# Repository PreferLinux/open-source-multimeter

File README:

The schematics and PCB layout are done in KiCAD.

Please see https://hackaday.io/project/10820-open-source-multimeter for details. There are also details in the schematics.

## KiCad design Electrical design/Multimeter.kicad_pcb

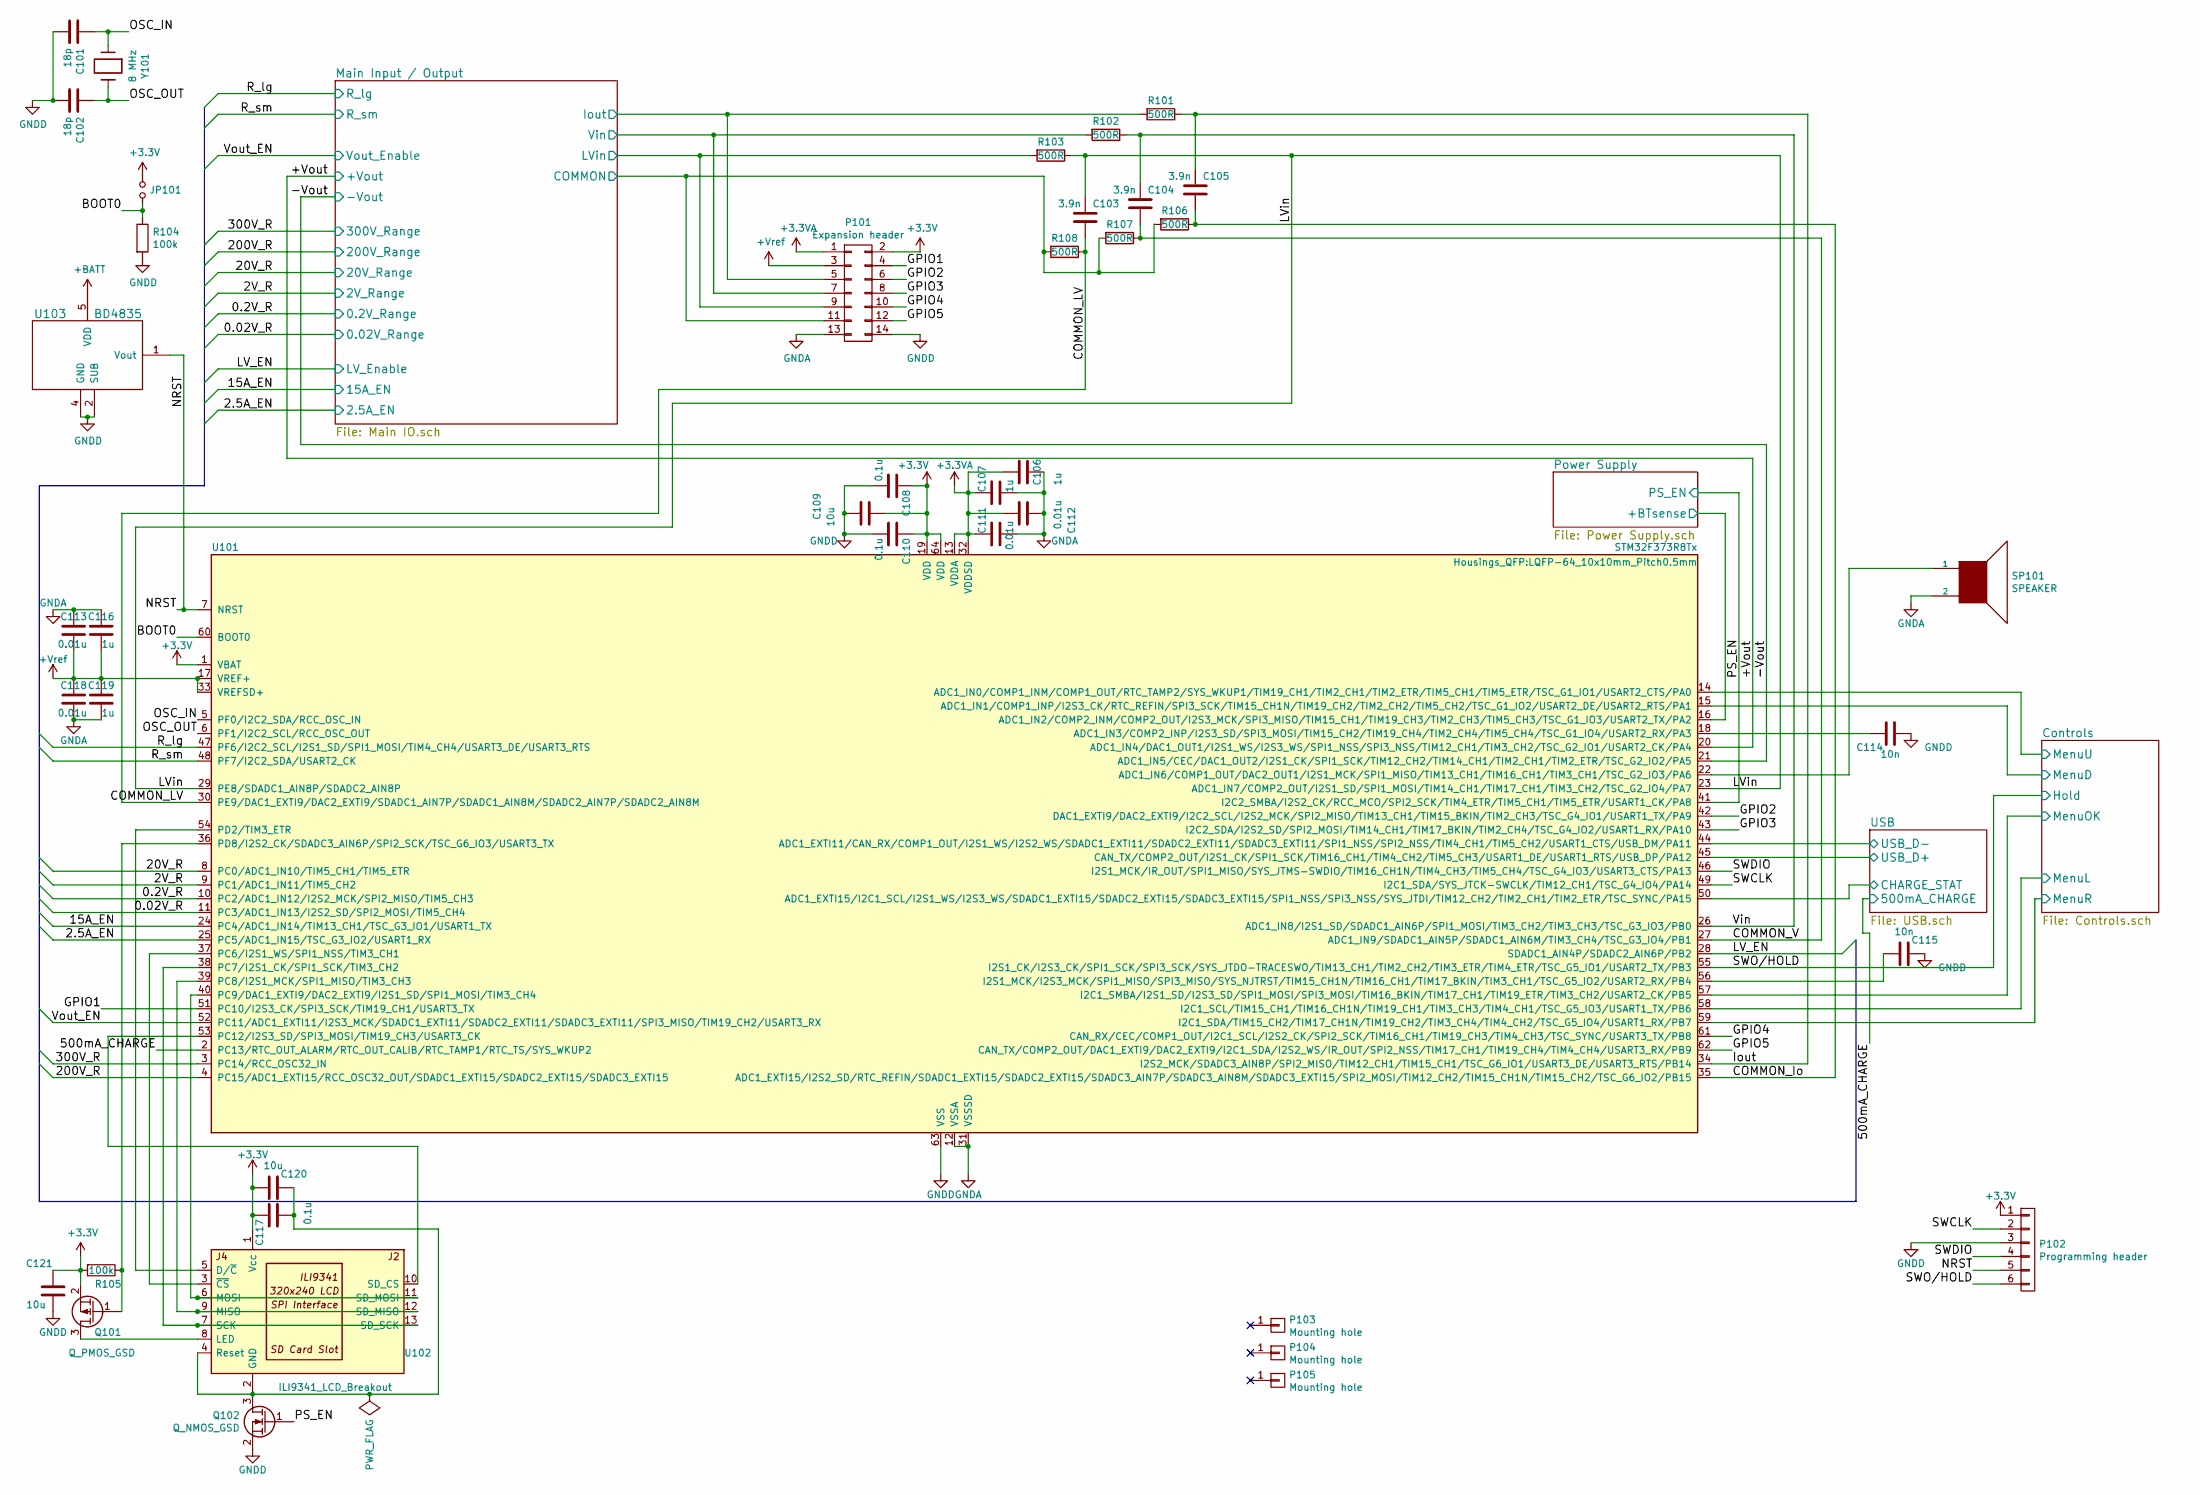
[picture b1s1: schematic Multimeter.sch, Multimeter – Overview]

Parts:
C101, C102: 18p; SMDuniversal_0603to0805_HandSoldering
C103, C104, C105: 3.9n; SMDuniversal_0603to0805_HandSoldering
C106, C107, C116, C119: 1u; SMDuniversal_0603to0805_HandSoldering
C108, C110, C117: 0.1u; SMDuniversal_0603to0805_HandSoldering
C109, C120, C121: 10u; SMDuniversal_0603to1206_HandSoldering
C111, C112, C113, C118: 0.01u; SMDuniversal_0603to0805_HandSoldering
C114, C115: 10n; SMDuniversal_0603to0805_HandSoldering
JP101: BOOT0; Pin_Header_Straight_1x02
P101: Expansion header; Pin_Header_Straight_2x07
P102: Programming header; Pin_Header_Straight_1x06
P103, P104, P105: Mounting hole; MountingHole_3.2mm_M3
Q101: Q_PMOS_GSD; SOT-23
Q102: Q_NMOS_GSD; SOT-23
R101, R102, R103, R106, R107, R108: 500R; SMDuniversal_0603to1210_HandSoldering
R104, R105: 100k; SMDuniversal_0603to1210_HandSoldering
SP101: SPEAKER; Pin_Header_Straight_1x02
U101: STM32F373R8Tx; LQFP-64_10x10mm_Pitch0.5mm
U102: ILI9341_LCD_Breakout
U103: BD4835; VSOF5_HandSoldering
Y101: 8 MHz; Crystal_HC49-SD_SMD

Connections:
+3.3VA: C106.2, C107.2, C111.2, C112.2, P101.1, U101.13 (VDDA), U101.32 (VDDSD); also elsewhere on the board
+3V3: C108.1, C109.2, C110.1, C117.1, C120.2, C121.1, JP101.1, P101.2, P102.1, Q101.2 (S), R105.2, U101.1 (VBAT), U101.19 (VDD), U101.64 (VDD), U102.1 (Vcc); also elsewhere on the board
+BATT: U103.5 (VDD); also elsewhere on the board
+Vref: C113.1, C116.1, C118.2, C119.2, P101.3, U101.17 (VREF+), U101.33 (VREFSD+); also elsewhere on the board
/0.2V_R: U101.10 (PC2/ADC1_IN12/I2S2_MCK/SPI2_MISO/TIM5_C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); also elsewhere on the board
/0.02V_R: U101.11 (PC3/ADC1_IN13/I2S2_SD/SPI2_MOSI/TIM5_CH4); also elsewhere on the board
/2.5A_EN: U101.25 (PC5/ADC1_IN15/TSC_G3_IO2/USART1_RX); also elsewhere on the board
/2V_R: U101.9 (PC1/ADC1_IN11/TIM5_CH2); also elsewhere on the board
/15A_EN: U101.24 (PC4/ADC1_IN14/TIM13_CH1/TSC_G3_IO1/USAR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); also elsewhere on the board
/20V_R: U101.8 (PC0/ADC1_IN10/TIM5_CH1/TIM5_ETR); also elsewhere on the board
/200V_R: U101.4 (PC15/ADC1_EXTI15/RCC_OSC32_OUT/SDADC1_E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); also elsewhere on the board
/300V_R: U101.3 (PC14/RCC_OSC32_IN); also elsewhere on the board
/500mA_CHARGE: U101.2 (PC13/RTC_OUT_ALARM/RTC_OUT_CALIB/RTC_TA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); also elsewhere on the board
/+Vout: U101.20 (ADC1_IN4/DAC1_OUT1/I2S1_WS/I2S3_WS/SPI1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); also elsewhere on the board
/-Vout: U101.21 (ADC1_IN5/CEC/DAC1_OUT2/I2S1_CK/SPI1_SCK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); also elsewhere on the board
/BOOT0: JP101.2, R104.1, U101.60 (BOOT0)
/COMMON_Io: C105.2, R106.1, U101.35 (ADC1_EXTI15/I2S2_SD/RTC_REFIN/SDADC1_EX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)
/COMMON_LV: C103.2, R108.1, U101.30 (PE9/DAC1_EXTI9/DAC2_EXTI9/SDADC1_AIN7P/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)
/COMMON_V: C104.2, R107.1, U101.27 (ADC1_IN9/SDADC1_AIN5P/SDADC1_AIN6M/TIM3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)
/Controls/MenuD: U101.15 (ADC1_IN1/COMP1_INP/I2S3_CK/RTC_REFIN/SP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); also elsewhere on the board
/Controls/MenuL: U101.58 (I2C1_SCL/TIM15_CH1/TIM16_CH1N/TIM19_CH1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); also elsewhere on the board
/Controls/MenuOK: U101.57 (I2C1_SMBA/I2S1_SD/I2S3_SD/SPI1_MOSI/SPI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); also elsewhere on the board
/Controls/MenuR: U101.59 (I2C1_SDA/TIM15_CH2/TIM17_CH1N/TIM19_CH2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); also elsewhere on the board
/Controls/MenuU: U101.14 (ADC1_IN0/COMP1_INM/COMP1_OUT/RTC_TAMP2/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); also elsewhere on the board
/GPIO1: P101.4, U101.51 (PC10/I2S3_CK/SPI3_SCK/TIM19_CH1/USART3_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)
/GPIO2: P101.6, U101.42 (DAC1_EXTI9/DAC2_EXTI9/I2C2_SCL/I2S2_MCK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)
/GPIO3: P101.8, U101.43 (I2C2_SDA/I2S2_SD/SPI2_MOSI/TIM14_CH1/TI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)
/GPIO4: P101.10, U101.61 (CAN_RX/CEC/COMP1_OUT/I2C1_SCL/I2S2_CK/S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)
/GPIO5: P101.12, U101.62 (CAN_TX/COMP2_OUT/DAC1_EXTI9/DAC2_EXTI9/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)
/Iout: C105.1, R101.1, U101.34 (I2S2_MCK/SDADC3_AIN8P/SPI2_MISO/TIM12_C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)
/LV_EN: U101.28 (SDADC1_AIN4P/SDADC2_AIN6P/PB2); also elsewhere on the board
/LVin: C103.1, R103.1, U101.23 (ADC1_IN7/COMP2_OUT/I2S1_SD/SPI1_MOSI/TI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), U101.29 (PE8/SDADC1_AIN8P/SDADC2_AIN8P)
/Main Input / Output/COMMON: P101.11, R106.2, R107.2, R108.2; also elsewhere on the board
/Main Input / Output/Iout: P101.5, R101.2; also elsewhere on the board
/Main Input / Output/LVin: P101.9, R103.2; also elsewhere on the board
/Main Input / Output/Vin: P101.7, R102.2; also elsewhere on the board
/NRST: P102.5, U101.7 (NRST), U103.1 (Vout)
/OSC_IN: C101.1, U101.5 (PF0/I2C2_SDA/RCC_OSC_IN), Y101.1
/OSC_OUT: C102.1, U101.6 (PF1/I2C2_SCL/RCC_OSC_OUT), Y101.2
/PS_EN: Q102.1 (G), U101.41 (I2C2_SMBA/I2S2_CK/RCC_MCO/SPI2_SCK/TIM4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); also elsewhere on the board
/Power Supply/+BTsense: U101.16 (ADC1_IN2/COMP2_INM/COMP2_OUT/I2S3_MCK/S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); also elsewhere on the board
/R_lg: U101.47 (PF6/I2C2_SCL/I2S1_SD/SPI1_MOSI/TIM4_CH4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); also elsewhere on the board
/R_sm: U101.48 (PF7/I2C2_SDA/USART2_CK); also elsewhere on the board
/SWCLK: P102.2, U101.49 (I2C1_SDA/SYS_JTCK-SWCLK/TIM12_CH1/TSC_G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)
/SWDIO: P102.4, U101.46 (I2S1_MCK/IR_OUT/SPI1_MISO/SYS_JTMS-SWDI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)
/SWO/HOLD: P102.6, U101.55 (I2S1_CK/I2S3_CK/SPI1_SCK/SPI3_SCK/SYS_J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); also elsewhere on the board
/USB/CHARGE_STAT: U101.50 (ADC1_EXTI15/I2C1_SCL/I2S1_WS/I2S3_WS/SD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); also elsewhere on the board
/USB/USB_D+: U101.45 (CAN_TX/COMP2_OUT/I2S1_CK/SPI1_SCK/TIM16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); also elsewhere on the board
/USB/USB_D-: U101.44 (ADC1_EXTI11/CAN_RX/COMP1_OUT/I2S1_WS/I2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); also elsewhere on the board
/Vin: C104.1, R102.1, U101.26 (ADC1_IN8/I2S1_SD/SDADC1_AIN6P/SPI1_MOSI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)
/Vout_EN: U101.52 (PC11/ADC1_EXTI11/I2S3_MCK/SDADC1_EXTI11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); also elsewhere on the board
GNDA: C106.1, C107.1, C111.1, C112.1, C113.2, C116.2, C118.1, C119.1, P101.13, SP101.2, U101.12 (VSSA), U101.31 (VSSSD); also elsewhere on the board
GNDD: C101.2, C102.2, C108.2, C109.1, C110.2, C114.1, C115.1, C121.2, P101.14, P102.3, Q102.2 (S), R104.2, U101.63 (VSS), U103.2 (SUB), U103.4 (GND); also elsewhere on the board
unnamed: C114.2, U101.18 (ADC1_IN3/COMP2_INP/I2S3_SD/SPI3_MOSI/TI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)
unnamed: C115.2, U101.56 (I2S1_MCK/I2S3_MCK/SPI1_MISO/SPI3_MISO/S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)
unnamed: C117.2, C120.1, Q102.3 (D), U102.2 (GND), U102.4 (Reset)
unnamed: Q101.1 (G), R105.1, U101.36 (PD8/I2S2_CK/SDADC3_AIN6P/SPI2_SCK/TSC_G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)
unnamed: Q101.3 (D), U102.8 (LED)
unnamed: SP101.1, U101.22 (ADC1_IN6/COMP1_OUT/DAC2_OUT1/I2S1_MCK/S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)
unnamed: U101.37 (PC6/I2S1_WS/SPI1_NSS/TIM3_CH1), U102.3 (~CS)
unnamed: U101.38 (PC7/I2S1_CK/SPI1_SCK/TIM3_CH2), U102.7 (SCK), U102.13 (SD_SCK)
unnamed: U101.39 (PC8/I2S1_MCK/SPI1_MISO/TIM3_CH3), U102.9 (MISO), U102.12 (SD_MISO)
unnamed: U101.40 (PC9/DAC1_EXTI9/DAC2_EXTI9/I2S1_SD/SPI1_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), U102.6 (MOSI), U102.11 (SD_MOSI)
unnamed: U101.53 (PC12/I2S3_SD/SPI3_MOSI/TIM19_CH3/USART3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), U102.10 (SD_CS)
unnamed: U101.54 (PD2/TIM3_ETR), U102.5 (D/~C)

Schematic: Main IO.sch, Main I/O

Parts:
C201, C202, C205: 0.1u; SMDuniversal_0603to0805_HandSoldering
C204, C206: 10u; SMDuniversal_0603to1206_HandSoldering
D201, D202, D203, D204: D; Diode_R-6_Horizontal_RM15
D205, D206, D213, D214: D_Schottky; SC-90A
D207, D208, D209, D210: TVS; SMB_Handsoldering
F201, F202: FUSE; Fuseholder6x32_horiz_open_inline_Type-I
JP201, JP203: Jumper_NO_Small; R_0603_HandSoldering
JP202, JP204: Jumper_NC_Small; R_0603_HandSoldering
P201: 10 A; Banana_Jack_1Pin
P202: mA; Banana_Jack_1Pin
P203: V R; Banana_Jack_1Pin_2Contact_SM_Top
P204: COMMON; Banana_Jack_1Pin_2Contact_SM_Top
Q201: Q_NMOS_GSD; SOT-23
R201: 10m; Resistor_SMD+THTuniversal_0805to2512_RM10_HandSoldering
R202: 100m; Resistor_SMD+THTuniversal_0805to2512_RM10_HandSoldering
R203, R211: 1k; SMDuniversal_0603to1210_HandSoldering
R204: 100R; SMDuniversal_0603to1210_HandSoldering
R205, R206, R207, R208: 1.8k; Resistor_SMDuniversal_0805to2512_HandSoldering
R209, R210, R216: 10k; SMDuniversal_0603to1210_HandSoldering
R212, R228: 100k; SMDuniversal_0603to1210_HandSoldering
R213, R214, R219, R224, R225, R231, R232, R233, R235, R237, R238: R; SMDuniversal_0603to1210_HandSoldering
R215: 100k; Resistor_Horizontal_RM20mm
R217, R218, R220, R221, R222, R223, R226, R227, R229, R230, R234, R236, R239, R240, R241, R242, R243, R244, R245, R246: 1M; SMDuniversal_0603to1210_HandSoldering
R247, R248, R249: 68R; SMDuniversal_0603to1210_HandSoldering
U201, U205: CT138; DIP-6_W7.62mm_LongPads
U202: MCP6002; MSOP-8_3x3mm_Pitch0.65mm
U203: MCP6N11; SOIC-8_3.9x4.9mm_Pitch1.27mm
U204, U206, U208, U209, U210, U211, U212, U213, U214, U215, U216, U217, U218: 74LVC1G66 GNDA; SOT-353
U207: TSV634; TSSOP-14_4.4x5mm_Pitch0.65mm
VR201, VR202, VR203, VR204: VR; RV_Disc_D15.5_W5.4_P7.5

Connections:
+3.3VA: C201.1, C204.1, C205.1, R245.1, U202.8 (V+), U203.7 (V+); also elsewhere on the board
+V_int: C202.1, C206.2, D205.1 (K), D213.1 (K), U204.5, U206.5, U207.4 (V+), U208.5, U209.5, U210.5, U211.5, U212.5, U213.5, U214.5, U215.5, U216.5, U217.5, U218.5; also elsewhere on the board
/0.2V_R: U215.4; also elsewhere on the board
/0.02V_R: U213.4; also elsewhere on the board
/2.5A_EN: U212.4; also elsewhere on the board
/2V_R: JP203.2, JP204.1, JP204.2, U217.4; also elsewhere on the board
/15A_EN: U210.4; also elsewhere on the board
/20V_R: JP201.2, JP202.1, JP202.2, JP203.1, U216.4; also elsewhere on the board
/200V_R: U211.4; also elsewhere on the board
/300V_R: U214.4; also elsewhere on the board
/+Vout: U202.3 (+); also elsewhere on the board
/-Vout: U202.5 (+); also elsewhere on the board
/LV_EN: R211.1, U208.4; also elsewhere on the board
/Main Input / Output/2.5A_Sense: D203.1 (K), D204.2 (A), F202.2, R202.2, U212.2
/Main Input / Output/15A_Sense: D201.1 (K), D202.2 (A), F201.2, R201.2, U210.2
/Main Input / Output/COM: R245.2, R246.1, R249.2, U207.12 (+), U209.1, U211.1, U214.1, U216.1
/Main Input / Output/COMMON: U204.1, U206.1, U207.13 (-), U207.14, U213.1, U215.1, U217.1; also elsewhere on the board
/Main Input / Output/COM_D: D201.2 (A), D202.1 (K), D203.2 (A), D204.1 (K), P204.1, R201.1, R202.1, R249.1, VR201.2, VR202.2, VR203.2, VR204.2
/Main Input / Output/Iout: R212.1, U203.6 (OUT); also elsewhere on the board
/Main Input / Output/LVin: R228.1, U207.7; also elsewhere on the board
/Main Input / Output/Vin: U207.8, U207.9 (-); also elsewhere on the board
/R_lg: U204.4; also elsewhere on the board
/R_sm: U206.4; also elsewhere on the board
/Vout_EN: Q201.1 (G), R203.1, U203.8 (EN/~CAL), U218.4; also elsewhere on the board
GNDA: C201.2, C202.2, C204.2, C206.1, D206.2 (A), D214.2 (A), Q201.2 (S), R246.2, U203.4 (V-), U204.3, U206.3, U207.11 (V-), U208.3, U209.3, U210.3, U211.3, U212.3, U213.3, U214.3, U215.3, U216.3, U217.3, U218.3; also elsewhere on the board
GNDD: U201.2, U205.2; also elsewhere on the board
unnamed: C205.2, Q201.3 (D), U202.4 (V-)
unnamed: D205.2 (A), D206.1 (K), R204.1, R209.2, R247.2
unnamed: D207.1, R206.1, R208.1, U201.4
unnamed: D207.2, D208.1
unnamed: D208.2, R204.2, R210.2, U201.6
unnamed: D209.1, R215.1, U205.4
unnamed: D209.2, D210.1
unnamed: D210.2, U205.6, U207.3 (+)
unnamed: D213.2 (A), D214.1 (K), P204.2, U218.2
unnamed: F201.1, P201.1
unnamed: F202.1, P202.1
unnamed: JP201.1, U209.4
unnamed: P203.1, R205.2, R207.2
unnamed: P203.2, R215.2, R217.2, VR201.1, VR202.1, VR203.1, VR204.1
unnamed: R203.2, U201.1
unnamed: R205.1, R206.2, R207.1, R208.2
unnamed: R209.1, U203.3 (+)
unnamed: R210.1, U203.2 (-)
unnamed: R211.2, U205.1
unnamed: R212.2, U203.1 (Vfg)
unnamed: R213.1, U204.2
unnamed: R213.2, R214.2, U203.5 (Vref)
unnamed: R214.1, U206.2
unnamed: R216.1, U208.1
unnamed: R216.2, U207.1, U207.2 (-)
unnamed: R217.1, R220.1
unnamed: R218.1, R219.2, R224.2, R232.2, R234.2, U207.10 (+)
unnamed: R218.2, R221.2
unnamed: R219.1, U209.2
unnamed: R220.2, R222.2
unnamed: R221.1, R223.1
unnamed: R222.1, R226.1
unnamed: R223.2, R227.2
unnamed: R224.1, R225.1, R225.2, U211.2
unnamed: R226.2, R229.2
unnamed: R227.1, R230.1
unnamed: R228.2, R231.2, R233.2, R238.2, U207.6 (-)
unnamed: R229.1, R230.2
unnamed: R231.1, U213.2
unnamed: R232.1, U214.2
unnamed: R233.1, U215.2
unnamed: R234.1, R236.1
unnamed: R235.1, U216.2
unnamed: R235.2, R237.1, R237.2, R240.1, R240.2, R242.1, R242.2, R243.1, R244.1, R244.2
unnamed: R236.2, R239.2
unnamed: R238.1, U217.2
unnamed: R239.1, R241.1
unnamed: R241.2, R243.2
unnamed: R247.1, U202.1, U202.2 (-)
unnamed: R248.1, U202.6 (-), U202.7
unnamed: R248.2, U218.1
unnamed: U207.5 (+), U208.2, U210.1, U212.1

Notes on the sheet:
0 – 150 mV (@ 15 A)
0 – 250 mV (@ 2.5 A)
The bottom set of jumpers allows switching the 2 V range between attenuation and amplification, and the top set allows switching the 20 V range to use the resistor string of the 2 V range when the 2 V range is set for amplification. Currently the 2 V range is used for amplification, and the 20 V ra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

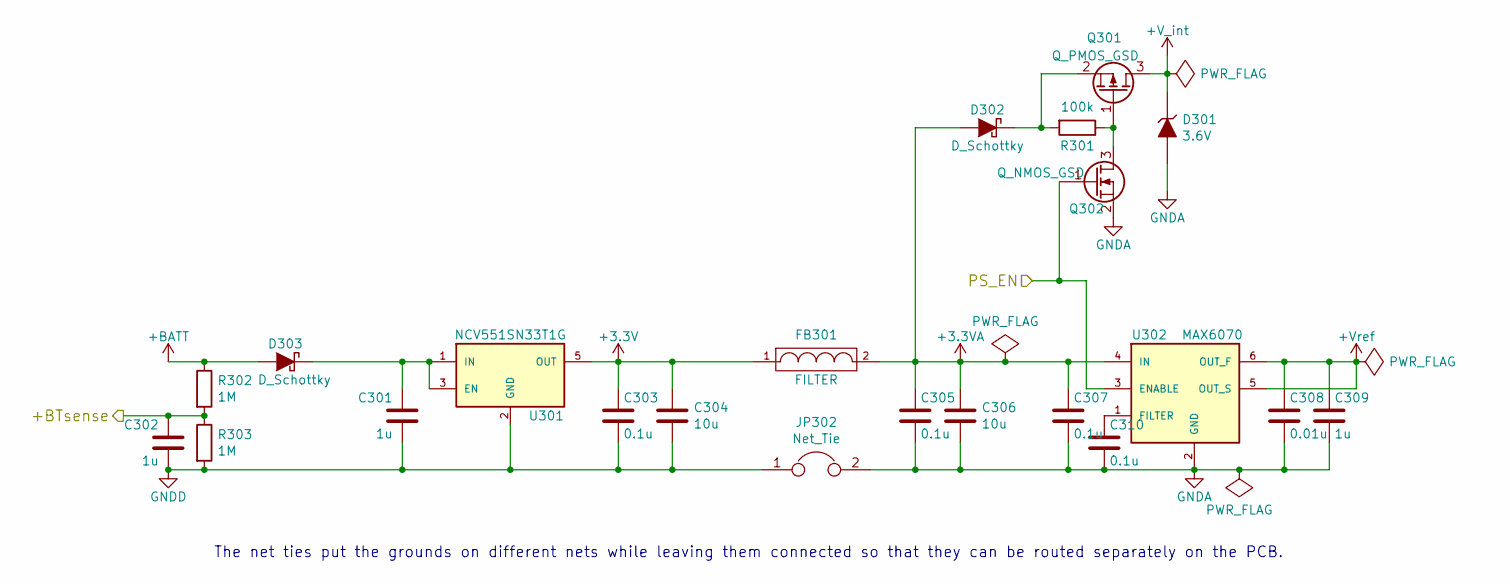
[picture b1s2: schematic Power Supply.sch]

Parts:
C301, C302, C309: 1u; SMDuniversal_0603to0805_HandSoldering
C303, C305, C307, C310: 0.1u; SMDuniversal_0603to0805_HandSoldering
C304, C306: 10u; SMDuniversal_0603to1206_HandSoldering
C308: 0.01u; SMDuniversal_0603to0805_HandSoldering
D301: 3.6V; SOT-23
D302, D303: D_Schottky; SC-90A
FB301: FILTER; SMDuniversal_0603to1210_HandSoldering
JP302: Net_Tie
Q301: Q_PMOS_GSD; SOT-23
Q302: Q_NMOS_GSD; SOT-23
R301: 100k; SMDuniversal_0603to1210_HandSoldering
R302, R303: 1M; SMDuniversal_0603to1210_HandSoldering
U301: NCV551SN33T1G; SOT-23-5
U302: MAX6070; SOT-23-6_Handsoldering

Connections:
+3.3VA: C305.1, C306.1, C307.1, D302.2 (A), FB301.2, U302.4 (IN); also elsewhere on the board
+3V3: C303.1, C304.1, FB301.1, U301.5 (OUT); also elsewhere on the board
+BATT: D303.2 (A), R302.1; also elsewhere on the board
+V_int: D301.3 (K), Q301.3 (D); also elsewhere on the board
+Vref: C308.1, C309.1, U302.5 (OUT_S), U302.6 (OUT_F); also elsewhere on the board
/PS_EN: Q302.1 (G), U302.3 (ENABLE); also elsewhere on the board
/Power Supply/+BTsense: C302.1, R302.2, R303.1; also elsewhere on the board
GNDA: C305.2, C306.2, C307.2, C308.2, C309.2, C310.2, D301.1 (A), JP302.2, Q302.2 (S), U302.2 (GND); also elsewhere on the board
GNDD: C301.2, C302.2, C303.2, C304.2, JP302.1, R303.2, U301.2 (GND); also elsewhere on the board
unnamed: C301.1, D303.1 (K), U301.1 (IN), U301.3 (EN)
unnamed: C310.1, U302.1 (FILTER)
unnamed: D302.1 (K), Q301.2 (S), R301.2
unnamed: Q301.1 (G), Q302.3 (D), R301.1

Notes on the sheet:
The net ties put the grounds on different nets while leaving them connected so that they can be routed separately on the PCB.

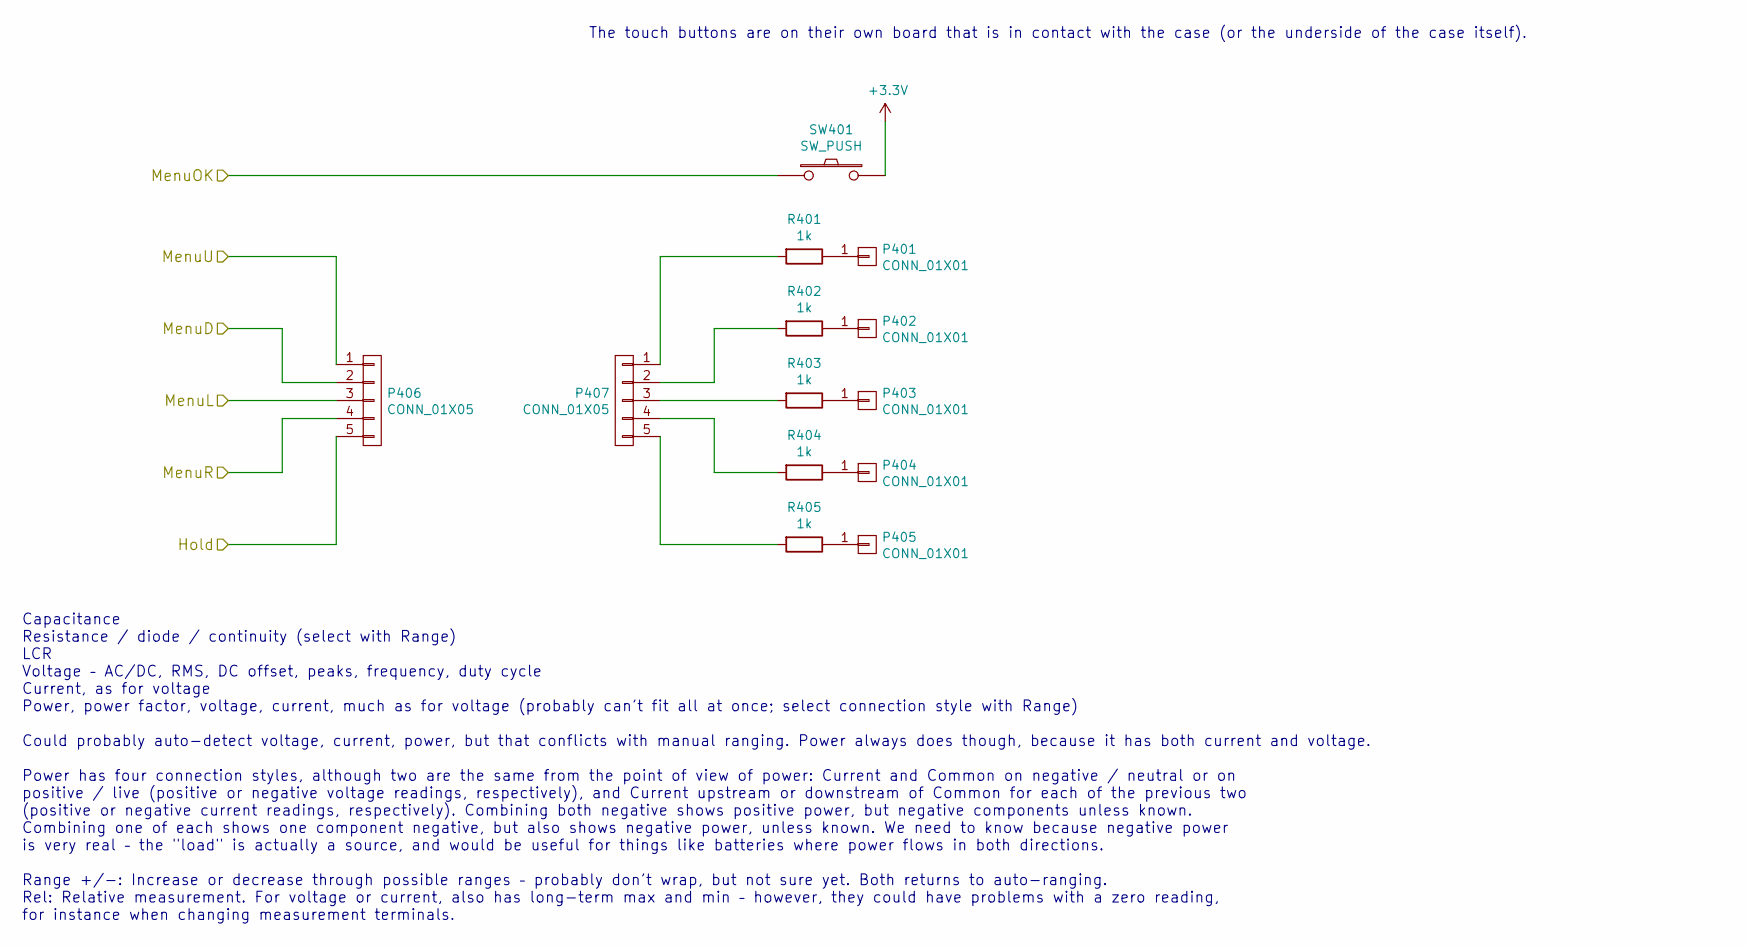
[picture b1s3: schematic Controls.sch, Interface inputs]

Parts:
P401, P402, P403, P404, P405: CONN_01X01; SolderWirePad_single_SMD_5x10mm
P406, P407: CONN_01X05; Pin_Header_Straight_1x05
R401, R402, R403, R404, R405: 1k; SMDuniversal_0603to1210_HandSoldering
SW401: SW_PUSH; SW_PUSH_SMALL

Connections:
+3V3: SW401.2; also elsewhere on the board
/Controls/MenuD: P406.2; also elsewhere on the board
/Controls/MenuL: P406.3; also elsewhere on the board
/Controls/MenuOK: SW401.1; also elsewhere on the board
/Controls/MenuR: P406.4; also elsewhere on the board
/Controls/MenuU: P406.1; also elsewhere on the board
/SWO/HOLD: P406.5; also elsewhere on the board
unnamed: P401.1, R401.1
unnamed: P402.1, R402.1
unnamed: P403.1, R403.1
unnamed: P404.1, R404.1
unnamed: P405.1, R405.1
unnamed: P407.1, R401.2
unnamed: P407.2, R402.2
unnamed: P407.3, R403.2
unnamed: P407.4, R404.2
unnamed: P407.5, R405.2

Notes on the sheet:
Capacitance Resistance / diode / continuity (select with Range) LCR Voltage – AC/DC, RMS, DC offset, peaks, frequency, duty cycle Current, as for voltage Power, power factor, voltage, current, much as for voltage (probably can't fit all at once; select connection style with Range) Could probably au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
The touch buttons are on their own board that is in contact with the case (or the underside of the case itself).

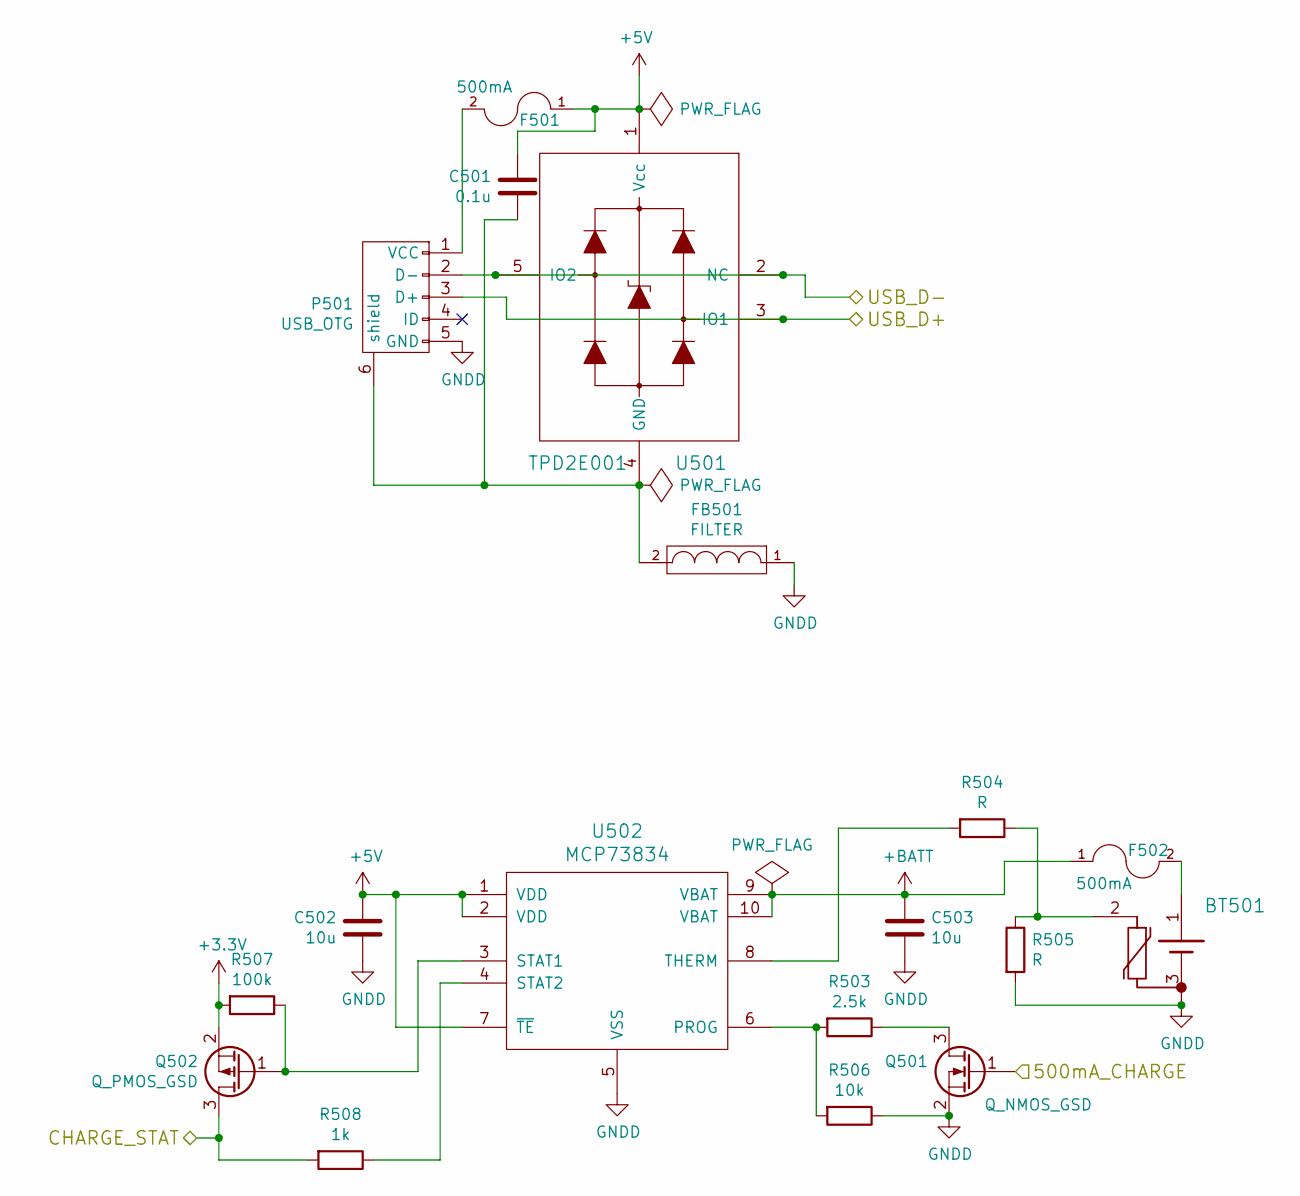
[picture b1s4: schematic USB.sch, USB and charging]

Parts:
BT501: Li-Ion_Cell; Pin_Header_Straight_1x03
C501: 0.1u; SMDuniversal_0603to0805_HandSoldering
C502, C503: 10u; SMDuniversal_0603to1206_HandSoldering
F501, F502: 500mA; R_1210_HandSoldering
FB501: FILTER; SMDuniversal_0603to1210_HandSoldering
P501: USB_OTG; MicroUSB_B_Vertical
Q501: Q_NMOS_GSD; SOT-23
Q502: Q_PMOS_GSD; SOT-23
R503: 2.5k; SMDuniversal_0603to1210_HandSoldering
R504, R505: R; SMDuniversal_0603to1210_HandSoldering
R506: 10k; SMDuniversal_0603to1210_HandSoldering
R507: 100k; SMDuniversal_0603to1210_HandSoldering
R508: 1k; SMDuniversal_0603to1210_HandSoldering
U501: TPD2E001; VSOF5_HandSoldering
U502: MCP73834; MSOP-10_3x3mm_Pitch0.5mm

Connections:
+3V3: Q502.2 (S), R507.2; also elsewhere on the board
+5V: C501.2, C502.1, F501.1, U501.1 (Vcc), U502.1 (VDD), U502.2 (VDD), U502.7 (~TE)
+BATT: C503.1, F502.1, U502.9 (VBAT), U502.10 (VBAT); also elsewhere on the board
/500mA_CHARGE: Q501.1 (G); also elsewhere on the board
/USB/CHARGE_STAT: Q502.3 (D), R508.2; also elsewhere on the board
/USB/USB_D+: P501.3 (D+), U501.3 (IO1); also elsewhere on the board
/USB/USB_D-: P501.2 (D-), U501.2 (NC), U501.5 (IO2); also elsewhere on the board
GNDD: BT501.3, C502.2, C503.2, FB501.1, P501.5 (GND), Q501.2 (S), R505.2, R506.1, U502.5 (VSS); also elsewhere on the board
unnamed: BT501.1, F502.2
unnamed: BT501.2, R504.1, R505.1
unnamed: C501.1, FB501.2, P501.6 (shield), U501.4 (GND)
unnamed: F501.2, P501.1 (VCC)
unnamed: Q501.3 (D), R503.1
unnamed: Q502.1 (G), R507.1, U502.3 (STAT1)
unnamed: R503.2, R506.2, U502.6 (PROG)
unnamed: R504.2, U502.8 (THERM)
unnamed: R508.1, U502.4 (STAT2)

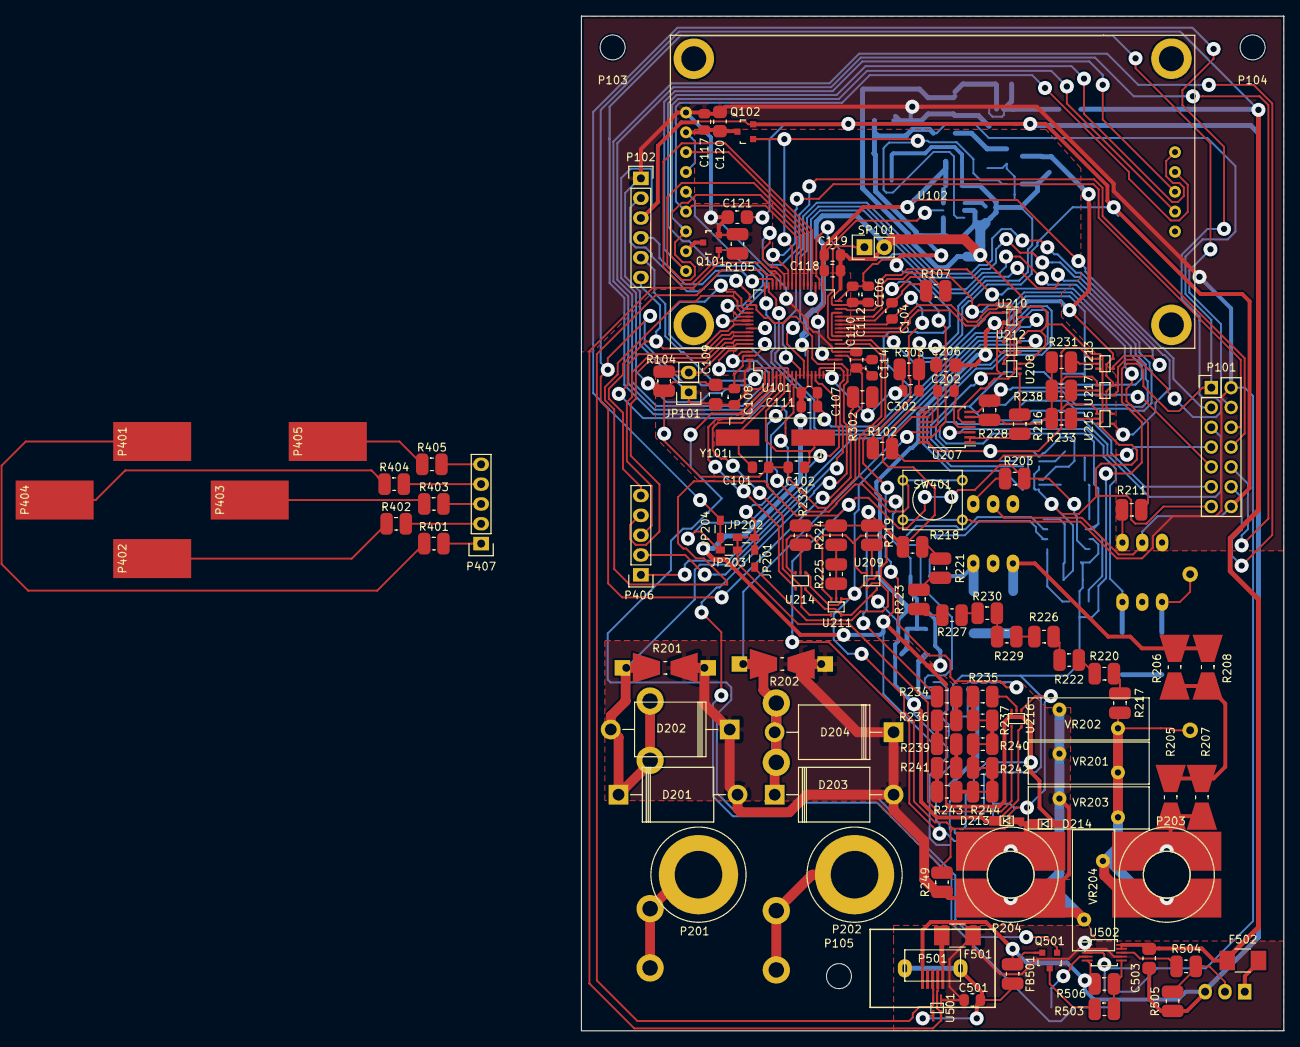
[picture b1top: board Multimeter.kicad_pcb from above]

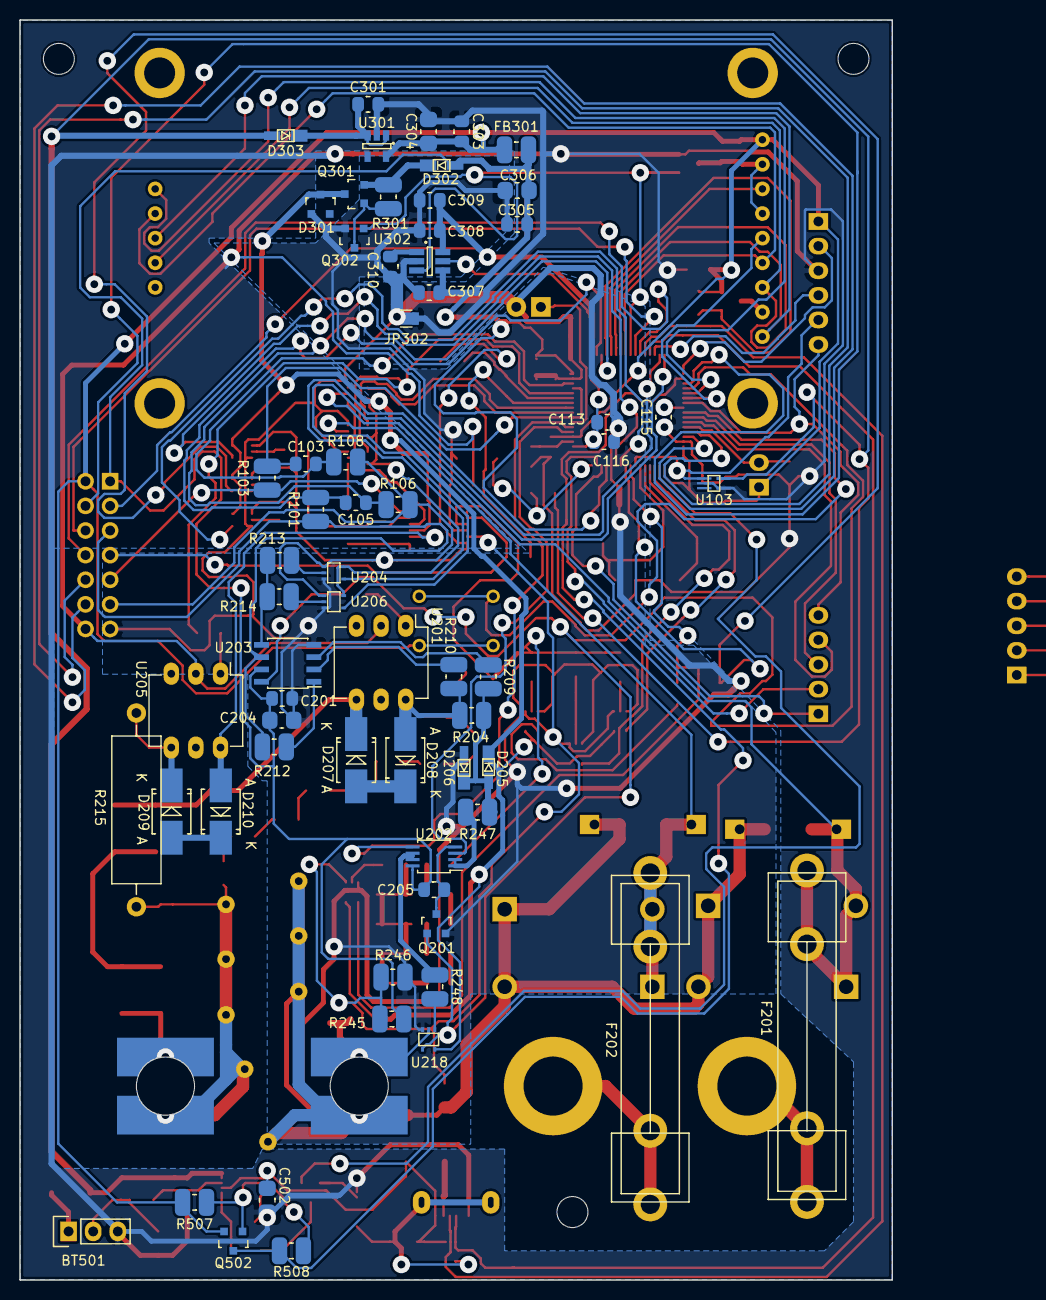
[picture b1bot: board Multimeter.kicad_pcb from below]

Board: 2 copper layers, 90.0 x 130.0 mm, 194 parts (64 on the bottom side), 146 nets.

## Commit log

2016-06-09 Initial design files. Schematics nearly finished except for component values.
2016-06-21 Updated schematics.
    Added speaker / buzzer, reset circuit (battery under-voltage lockout), changed battery charger IC.
    Altered Vout circuit.
    Added most resistor / capacitor values (those missing are either dependent on battery thermistor or ADC).
    Updated to show "correct" op-amps.
2016-06-21 Add battery voltage monitoring.
2016-06-22 Update External Design. Add battery sense capacitor. Update footprints.
2016-07-02 Added PCB layout.
    Also minor changes to schematic, the most major being changes
    to which MCU pins control what to make the PCB layout easier.
2016-07-04 Tied ground nets together, fixed clearance issues, added copper pours / zones.
2016-07-14 Add documentation. Fix some issues found while writing it.
    The issues fixed:
    Change R245-246 to 1M.
    Remove D211-212 and add D213-214.
    Power the analog switches from +V_int.
    Reconfigure range combination jumpers.
    Remove "GND" net.
2016-07-14 Added a resistor in COM to ensure clamping currents are handled correctly.
2016-07-14 Fix current circuit connection, PCB layout.
    The current measurement circuit has to connect directly to the Common terminal!
    The PCB layout had traces going between the pads of the Common terminal, where
    there's actually a non-plated hole. I've updated the footprint to include the hole,
    although unfortunately that produces about 20 DRC errors, and also re-routed stuff.
    Also updated the value of D301 to match a real Zener diode.
2016-07-17 Add STM32 breakout board. Update schematics PDF and docs.
    The PDF wasn't updated with the previous commit, but should have been. Likewise the documentation.
    The specific issue was the current measurement circuitry needed a direct connection to the Common terminal.
    The STM32 breakout board is for prototyping. Any QFP64 breakout boards I've seen have pins (or holes)
    on four sides, which is unsuitable for a breadboard. This is a simple breakout board if the net ties
    are cut and no components are placed. Otherwise it is actually a very minimal STM32F373 dev board.
2016-08-14 Connect the reset circuit to +BATT so that it actually works!
2016-08-24 Add the analog switch schematic component to the cache. Some PCB layout tweaks.

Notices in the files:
Electrical design/Controls.sch:
Licensed under the GNU GPL v3
